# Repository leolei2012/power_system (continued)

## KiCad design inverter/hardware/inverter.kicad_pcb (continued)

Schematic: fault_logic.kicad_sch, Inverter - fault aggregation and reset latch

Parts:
C55: 10n; C_0402_1005Metric; Voltage_Rating 25V; MPN TBD
Q8: MMBT3904LT1G; onsemi_SOT-23_CASE318_Recommended; MPN MMBT3904LT1G
R73, R74: 10k; R_0402_1005Metric; Tolerance 1%; MPN TBD
R75: 100k; R_0402_1005Metric; Tolerance 1%; MPN TBD
TP14: FAULT_LATCH; TestPoint_Pad_D1.5mm
U22, U23, U24, U25: 74LVC08APW,118; TSSOP-14_4.4x5mm_P0.65mm; MPN 74LVC08APW,118
U27: 74LVC00APW,118; TSSOP-14_4.4x5mm_P0.65mm; MPN 74LVC00APW,118
U28: 74LVC74AD,118; SOIC-14_3.9x8.7mm_P1.27mm; MPN 74LVC74AD,118

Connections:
+3V3_INV: U28.1 (~R); also elsewhere on the board
/Hardware latch/ENABLE_N: U24.10, U27.3
/Hardware latch/FAULT_ACTIVE: R74.1, U27.6
/Hardware latch/FAULT_BASE: Q8.1 (B), R74.2, R75.1
/Hardware latch/FAULT_LATCH: TP14.1, U28.5 (Q)
/Hardware latch/HEALTH_ALL: U24.6, U24.9, U24.12, U27.4, U28.4 (~S)
/Hardware latch/HEALTH_CHAIN_1: U22.3, U22.4
/Hardware latch/HEALTH_CHAIN_2: U22.6, U22.9
/Hardware latch/HEALTH_CHAIN_3: U22.8, U22.12
/Hardware latch/HEALTH_CHAIN_4: U22.11, U23.1
/Hardware latch/HEALTH_CHAIN_5: U23.3, U23.4
/Hardware latch/HEALTH_CHAIN_6: U23.6, U23.9
/Hardware latch/HEALTH_CHAIN_7: U23.8, U23.12
/Hardware latch/HEALTH_CHAIN_8: U23.11, U24.1
/Hardware latch/HEALTH_CHAIN_9: U24.3, U24.4
/Hardware latch/HEALTH_UNLATCHED: U24.11, U25.1
/Hardware latch/NO_LATCH: U24.13, U27.5, U28.6 (~Q)
/Hardware latch/RESET_CLK: C55.1, R73.2, U28.3 (C)
/Hardware latch/RESET_REQUEST: R73.1, U24.8
AUX_FLT_N: U24.5; also elsewhere on the board
BASE_LOGIC_OK: U23.13; also elsewhere on the board
BUS_OV_OK: U23.5; also elsewhere on the board
DRIVE_PERMIT: U25.3; also elsewhere on the board
DRV_PG_LOGIC: U24.2; also elsewhere on the board
DRV_UV_OK: U23.10; also elsewhere on the board
ENABLE_QUALIFIED: U25.2, U27.1, U27.2; also elsewhere on the board
FAULT_N: Q8.3 (C); also elsewhere on the board
OC_U_HIGH_OK: U22.1; also elsewhere on the board
OC_U_LOW_OK: U22.2; also elsewhere on the board
OC_V_HIGH_OK: U22.5; also elsewhere on the board
OC_V_LOW_OK: U22.10; also elsewhere on the board
OC_W_HIGH_OK: U22.13; also elsewhere on the board
OC_W_LOW_OK: U23.2; also elsewhere on the board

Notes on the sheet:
HARDWARE HEALTH CHAIN / EVERY INPUT MUST REMAIN HIGH
FAULT MEMORY / DELIBERATE DISABLE-TO-RESET / PERMISSION
/S=HEALTH_ALL; /R held HIGH; D=0. Fault asynchronously sets Q. RESET_REQUEST = HEALTH_ALL AND NOT ENABLE_QUALIFIED. 10k / 10n delays the rising reset clock; hold ENABLE low >=1 ms after recovery. Fault or invalid supplies block DRIVE_PERMIT directly. Recovery with ENABLE high cannot clear the latch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

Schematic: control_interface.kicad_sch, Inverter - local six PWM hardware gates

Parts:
C56, C57, C58, C59, C60, C61: 100n; C_0402_1005Metric; Voltage_Rating 25V; MPN TBD
R76, R77, R78, R79, R80, R81, R82: 10k; R_0402_1005Metric; Tolerance 1%; MPN TBD
R83: 100k; R_0402_1005Metric; Tolerance 1%; MPN TBD
U22, U23, U24, U25, U26: 74LVC08APW,118; TSSOP-14_4.4x5mm_P0.65mm; MPN 74LVC08APW,118
U27: 74LVC00APW,118; TSSOP-14_4.4x5mm_P0.65mm; MPN 74LVC00APW,118

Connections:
+3V3_INV: C56.1, C57.1, C58.1, C59.1, C60.1, C61.1, U22.14 (VCC), U23.14 (VCC), U24.14 (VCC), U25.14 (VCC), U26.14 (VCC), U27.14 (VCC); also elsewhere on the board
DRIVE_PERMIT: R83.1, U25.5, U25.10, U25.13, U26.2, U26.5, U26.10; also elsewhere on the board
ENABLE_IN: R82.1; also elsewhere on the board
PWM_UH_IN: R76.1, U25.4; also elsewhere on the board
PWM_UL_IN: R77.1, U25.9; also elsewhere on the board
PWM_VH_IN: R78.1, U25.12; also elsewhere on the board
PWM_VL_IN: R79.1, U26.1; also elsewhere on the board
PWM_WH_IN: R80.1, U26.4; also elsewhere on the board
PWM_WL_IN: R81.1, U26.9; also elsewhere on the board
U_HIN: U25.6; also elsewhere on the board
U_LIN: U25.8; also elsewhere on the board
V_HIN: U25.11; also elsewhere on the board
V_LIN: U26.3; also elsewhere on the board
W_HIN: U26.6; also elsewhere on the board
W_LIN: U26.8; also elsewhere on the board

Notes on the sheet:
HARDWARE GATING / SIX PWM COMMANDS
LOGIC POWER / LOCAL DECOUPLING
DEFAULT DISABLE / NO PERMISSION
R76-R81: hold all six commands LOW while the controller is disconnected or Hi-Z. R82: default disabled. R83: default no permission. Logic levels remain 3.3 V; hardware AND gates operate independently of firmware.
C56-C61: 100 nF local bypass at each logic package.
U26D / U27C / U27D are used on the Base interlock page. R76-R81 default PWM LOW; R82 raw ENABLE default LOW. No MCU on this board; CTRL_READY must qualify ENABLE before any latch reset or DRIVE_PERMIT.

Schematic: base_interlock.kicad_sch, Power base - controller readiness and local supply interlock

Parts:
R160: 10k; R_0402_1005Metric; Tolerance 1%; MPN TBD
U26: 74LVC08APW,118; TSSOP-14_4.4x5mm_P0.65mm; MPN 74LVC08APW,118
U27: 74LVC00APW,118; TSSOP-14_4.4x5mm_P0.65mm; MPN 74LVC00APW,118

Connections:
/Base interlock/BASE_NOT_READY: U27.8, U27.12, U27.13
BASE_LOGIC_OK: U27.9; also elsewhere on the board
BASE_READY: U27.11; also elsewhere on the board
CTRL_READY: R160.1, U26.13; also elsewhere on the board
DRV_PG_LOGIC: U27.10; also elsewhere on the board
ENABLE_IN: U26.12; also elsewhere on the board
ENABLE_QUALIFIED: U26.11; also elsewhere on the board

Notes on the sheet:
REMOVABLE CONTROLLER / DEFAULT DISABLE
Common GND, 3.3 V logic. CTRL_READY comes from the controller reset-health buffer. The power base owns all PWM pull-downs and hardware permission; no MCU firmware is required to block a missing controller.
R160 = 10k. Unplugged, controller reset or lost controller power => ENABLE_QUALIFIED LOW. Only ENABLE_QUALIFIED enters the latch reset and DRIVE_PERMIT logic. Raw ENABLE_IN keeps its original local R82 pull-down.
BASE SUPPLY PRESENCE / INDEPENDENT OF OPEN-COLLECTOR FAULT
BASE_READY = BASE_LOGIC_OK AND DRV_PG_LOGIC. The MCU sub-board provides its receiver pull-down. FAULT_N remains Q8 open collector with a pull-up only in the MCU 3.3 V domain. A high FAULT_N alone does not prove base power. U26/U27 package power and 100 nF bypass stay on Hardware PWM gates. No added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

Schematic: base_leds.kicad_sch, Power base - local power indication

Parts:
D3: PWR; LED_0603_1608Metric; MPN TBD
R130: 2.2k; R_0402_1005Metric; Tolerance 1%; MPN TBD

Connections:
+3V3_INV: R130.1; also elsewhere on the board
/Base LEDs/LED_PWR_AN: D3.2 (A), R130.2

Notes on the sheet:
LOCAL POWER INDICATOR / NO MCU LED SIGNALS ACROSS HEADER
D3: base 3.3 V present. This lamp alone does not indicate driver power or protection permission. D4..D7 and R131..R134 belong to the removable MCU sub-board: RUN / FAULT / COMM / AUX. The power base has no MCU-run or communication LED nets on its board-to-board header.

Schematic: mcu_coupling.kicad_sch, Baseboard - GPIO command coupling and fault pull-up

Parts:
R135, R136, R137, R138, R139, R140, R141, R142: 33; R_0402_1005Metric; Tolerance 1%; MPN TBD
R143: 10k; R_0402_1005Metric; Tolerance 1%; MPN TBD

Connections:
+3V3_CORE_REF: R143.2; also elsewhere on the board
BRAKE_IN: R142.2; also elsewhere on the board
ENABLE_IN: R141.2; also elsewhere on the board
PA8: R135.1; also elsewhere on the board
PA9: R137.1; also elsewhere on the board
PA10: R139.1; also elsewhere on the board
PB12: R143.1; also elsewhere on the board
PB13: R136.1; also elsewhere on the board
PB14: R138.1; also elsewhere on the board
PB15: R140.1; also elsewhere on the board
PC4: R141.1; also elsewhere on the board
PC6: R142.1; also elsewhere on the board
PWM_UH_IN: R135.2; also elsewhere on the board
PWM_UL_IN: R136.2; also elsewhere on the board
PWM_VH_IN: R137.2; also elsewhere on the board
PWM_VL_IN: R138.2; also elsewhere on the board
PWM_WH_IN: R139.2; also elsewhere on the board
PWM_WL_IN: R140.2; also elsewhere on the board

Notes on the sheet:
CONTROLLER COMMAND SERIES RESISTORS / BASEBOARD SIGNALS
FAULT INPUT / LOCAL PULL-UP AND TIMER BKIN
Protected PB12 is TIM1 BKIN; pull-up uses the exported core 3V3 reference. NRST is debug-only; it is not a power-stage fault output. Six PWM, ENABLE and BRAKE series resistors remain local to the base.

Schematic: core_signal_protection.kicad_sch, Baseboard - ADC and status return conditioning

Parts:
C69, C70, C71, C72, C73, C74, C75, C76: 1n; C_0402_1005Metric; Voltage_Rating 16 V minimum; MPN TBD
D201, D202, D203, D204, D205, D206, D207, D208, D209, D210: BAT54S,215; Nexperia_SOT23_Reflow_Pad0.70x0.60mm; MPN BAT54S,215
R84, R85, R86, R87, R88, R89, R90, R91: 100; R_0402_1005Metric; Tolerance 1%; MPN TBD
R201, R202, R203, R204, R205, R206, R207, R208: 360; R_0603_1608Metric; Tolerance 1%; MPN TBD
R209: 10k; R_0603_1608Metric; MPN TBD
R210, R211: 1k; R_0603_1608Metric; Tolerance 1%; MPN TBD

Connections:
+3V3_CORE_REF: D201.2 (K2), D202.2 (K2), D203.2 (K2), D204.2 (K2), D205.2 (K2), D206.2 (K2), D207.2 (K2), D208.2 (K2), D209.2 (K2), D210.2 (K2); also elsewhere on the board
BASE_READY: R210.1; also elsewhere on the board
FAULT_N: R211.1; also elsewhere on the board
I_U_PORT: R201.1; also elsewhere on the board
I_V_PORT: R202.1; also elsewhere on the board
I_W_PORT: R203.1; also elsewhere on the board
unnamed: D201.3 (K1/A2), R84.1, R201.2
unnamed: D202.3 (K1/A2), R85.1, R202.2
unnamed: D203.3 (K1/A2), R86.1, R203.2
unnamed: D204.3 (K1/A2), R87.1, R204.2
unnamed: D205.3 (K1/A2), R88.1, R205.2
unnamed: D206.3 (K1/A2), R89.1, R206.2
unnamed: D207.3 (K1/A2), R90.1, R207.2
unnamed: D208.3 (K1/A2), R91.1, R208.2
PA4: C73.1, R88.2; also elsewhere on the board
PB0: C74.1, R89.2; also elsewhere on the board
PB1: C75.1, R90.2; also elsewhere on the board
PB2: C76.1, R91.2; also elsewhere on the board
PB12: D210.3 (K1/A2), R211.2; also elsewhere on the board
PC0: C69.1, R84.2; also elsewhere on the board
PC1: C70.1, R85.2; also elsewhere on the board
PC2: C71.1, R86.2; also elsewhere on the board
PC3: C72.1, R87.2; also elsewhere on the board
PC13: D209.3 (K1/A2), R209.1, R210.2; also elsewhere on the board
TEMP_NTC: R208.1; also elsewhere on the board
V_DC_PORT: R204.1; also elsewhere on the board
V_U_PORT: R205.1; also elsewhere on the board
V_V_PORT: R206.1; also elsewhere on the board
V_W_PORT: R207.1; also elsewhere on the board

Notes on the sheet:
STATUS RETURN LIMITING / CORE-REFERENCED CLAMPS
8 ADC PATHS / 360R CLAMP + 100R / 1n AT CORE SOCKET
I_U_PORT -> PC0
I_V_PORT -> PC1
I_W_PORT -> PC2
V_DC_PORT -> PC3
V_U_PORT -> PA4
V_V_PORT -> PB0
V_W_PORT -> PB1
TEMP_NTC -> PB2
Clamp upper rail returns ONLY through core 3V3_REF pins; never join it to base +3V3_INV. Power off both boards before mating.

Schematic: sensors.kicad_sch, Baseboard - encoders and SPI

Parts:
J9: ENC_A: PWR GND A B Z; HCTL_PZ127_1x05_P1.27mm_Drill0.70mm; MPN PZ127-1-05-Z
J10: ENC_B: PWR GND A B Z; HCTL_PZ127_1x05_P1.27mm_Drill0.70mm; MPN PZ127-1-05-Z
J11: SPI_A: PWR GND SCK MOSI MISO CS; HCTL_PZ127_1x06_P1.27mm_Drill0.70mm; MPN PZ127-1-06-Z
J12: SPI_B: PWR GND SCK MOSI MISO CS; HCTL_PZ127_1x06_P1.27mm_Drill0.70mm; MPN PZ127-1-06-Z
R94, R96, R98, R101, R103, R105: 100; R_0402_1005Metric; Tolerance 1%; MPN TBD
R95, R97, R99, R102, R104, R106, R112, R118: 10k; R_0402_1005Metric; Tolerance 1%; MPN TBD
R100, R107, R113, R119: 0; R_0402_1005Metric; Tolerance 1%; MPN TBD; not fitted
R108, R109, R110, R111, R114, R115, R116, R117: 33; R_0402_1005Metric; Tolerance 1%; MPN TBD

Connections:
+3V3_INV: R95.2, R97.2, R99.2, R102.2, R104.2, R106.2, R112.2, R118.2; also elsewhere on the board
+5V_SENSOR: R100.1, R107.1, R113.1, R119.1; also elsewhere on the board
/Encoders and SPI/ENC_A_A_PORT: J9.3, R94.1
/Encoders and SPI/ENC_A_B_PORT: J9.4, R96.1
/Encoders and SPI/ENC_A_VCC: J9.1, R100.2
/Encoders and SPI/ENC_A_Z_PORT: J9.5, R98.1
/Encoders and SPI/ENC_B_A_PORT: J10.3, R101.1
/Encoders and SPI/ENC_B_B_PORT: J10.4, R103.1
/Encoders and SPI/ENC_B_VCC: J10.1, R107.2
/Encoders and SPI/ENC_B_Z_PORT: J10.5, R105.1
/Encoders and SPI/SPI_A_CS_PORT: J11.6, R111.2
/Encoders and SPI/SPI_A_MISO_PORT: J11.5, R110.2
/Encoders and SPI/SPI_A_MOSI_PORT: J11.4, R109.2
/Encoders and SPI/SPI_A_SCK_PORT: J11.3, R108.2
/Encoders and SPI/SPI_A_VCC: J11.1, R113.2
/Encoders and SPI/SPI_B_CS_PORT: J12.6, R117.2
/Encoders and SPI/SPI_B_MISO_PORT: J12.5, R116.2
/Encoders and SPI/SPI_B_MOSI_PORT: J12.4, R115.2
/Encoders and SPI/SPI_B_SCK_PORT: J12.3, R114.2
/Encoders and SPI/SPI_B_VCC: J12.1, R119.2
PA0: R94.2, R95.1; also elsewhere on the board
PA1: R96.2, R97.1; also elsewhere on the board
PA2: R98.2, R99.1; also elsewhere on the board
PA3: R105.2, R106.1; also elsewhere on the board
PA5: R108.1; also elsewhere on the board
PA6: R110.1; also elsewhere on the board
PA7: R109.1; also elsewhere on the board
PA15: R111.1, R112.1; also elsewhere on the board
PB6: R101.2, R102.1; also elsewhere on the board
PB7: R103.2, R104.1; also elsewhere on the board
PC9: R117.1, R118.1; also elsewhere on the board
PC10: R114.1; also elsewhere on the board
PC11: R116.1; also elsewhere on the board
PC12: R115.1; also elsewhere on the board

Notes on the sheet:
ABZ ENCODER A / 3.3 V SINGLE-ENDED
DNP
100 ohm series / 10k pull-ups to 3.3 V. 5 V supply link DNP.
SPI SENSOR A / 3.3 V SINGLE-ENDED
ABZ ENCODER B / 3.3 V SINGLE-ENDED
SPI SENSOR B / 3.3 V SINGLE-ENDED
All external signal pins are 3.3 V single-ended; no 5 V level conversion or cable protection is claimed. R100 / R107 / R113 / R119 are DNP: external sensor-power links remain open by default.

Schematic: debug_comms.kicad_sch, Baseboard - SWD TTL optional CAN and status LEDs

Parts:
C82: 100n; C_0402_1005Metric; Voltage_Rating 16 V minimum; MPN TBD; not fitted
D4: LED_RUN; LED_0603_1608Metric; MPN TBD
D5: LED_FAULT; LED_0603_1608Metric; MPN TBD
D6: LED_COMM; LED_0603_1608Metric; MPN TBD
D7: LED_AUX; LED_0603_1608Metric; MPN TBD
J13: SWD: VTREF IO CLK GND NRST; HCTL_PZ127_1x05_P1.27mm_Drill0.70mm; MPN PZ127-1-05-Z
J14: TTL: TX RX GND; HCTL_PZ127_1x03_P1.27mm_Drill0.70mm; MPN PZ127-1-03-Z
J15: CAN: H L GND; HCTL_PZ127_1x03_P1.27mm_Drill0.70mm; MPN PZ127-1-03-Z; not fitted
R120, R121, R123: 33; R_0402_1005Metric; Tolerance 1%; MPN TBD
R124: 100; R_0402_1005Metric; Tolerance 1%; MPN TBD
R125: 10k; R_0402_1005Metric; Tolerance 1%; MPN TBD
R126, R127: 0; R_0402_1005Metric; Tolerance 1%; MPN TBD; not fitted
R128: 10k; R_0402_1005Metric; Tolerance 1%; MPN TBD; not fitted
R129: 120; R_0402_1005Metric; Tolerance 1%; MPN TBD; not fitted
R131, R132, R133, R134: 2.2k; R_0402_1005Metric; Tolerance 1%; MPN TBD
U31: SN65HVD232DR; SOIC-8_3.9x4.9mm_P1.27mm; MPN SN65HVD232DR; not fitted

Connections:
+3V3_CORE_REF: J13.1; also elsewhere on the board
+3V3_INV: C82.1, R125.2, R128.2, R131.1, R132.1, R133.1, R134.1, U31.3 (VCC); also elsewhere on the board
/SWD UART CAN and status/CAN_H: J15.1, R129.1, U31.7 (CANH)
/SWD UART CAN and status/CAN_L: J15.2, R129.2, U31.6 (CANL)
/SWD UART CAN and status/CAN_RX_PHY: R127.1, U31.4 (R)
/SWD UART CAN and status/CAN_TX_PHY: R126.2, R128.1, U31.1 (D)
/SWD UART CAN and status/LED_AN_1: D4.2 (A), R131.2
/SWD UART CAN and status/LED_AN_2: D5.2 (A), R132.2
/SWD UART CAN and status/LED_AN_3: D6.2 (A), R133.2
/SWD UART CAN and status/LED_AN_4: D7.2 (A), R134.2
/SWD UART CAN and status/SWCLK_PORT: J13.3, R121.1
/SWD UART CAN and status/SWDIO_PORT: J13.2, R120.1
/SWD UART CAN and status/UART_RX_PORT: J14.2, R124.1
/SWD UART CAN and status/UART_TX_PORT: J14.1, R123.2
NRST: J13.5; also elsewhere on the board
PA11: R127.2; also elsewhere on the board
PA12: R126.1; also elsewhere on the board
PA13: R120.2; also elsewhere on the board
PA14: R121.2; also elsewhere on the board
PB5: D7.1 (K); also elsewhere on the board
PB10: R123.1; also elsewhere on the board
PB11: R124.2, R125.1; also elsewhere on the board
PC5: D4.1 (K); also elsewhere on the board
PC8: D5.1 (K); also elsewhere on the board
PD2: D6.1 (K); also elsewhere on the board

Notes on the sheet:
SWD / OPEN-DRAIN RESET / BOOT
VTREF senses the core 3V3 reference. NRST goes only to the core reset domain. RESET / BOOT buttons are on the minimum-system core. Existing TTL PB10/PB11 is application UART, not the ROM USART3 pin pair.
TTL UART / USART3 / 3.3 V
TX/RX relative to this board; no RS-232 levels. No USB and no supply output on TTL connector.
OPTIONAL CLASSIC CAN / COMPLETE PHY BLOCK DNP
FOUR MCU STATUS INDICATORS / ACTIVE LOW

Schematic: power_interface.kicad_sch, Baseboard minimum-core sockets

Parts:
J101, J102: PM254V-12-32-H85; XFCN_PM254V-12-32-H85_2x16_P2.54mm_Vertical_Drill1.02mm; MPN PM254V-12-32-H85
TP16: FAULT_N; TestPoint_Pad_D1.5mm
TP17: ENABLE_IN; TestPoint_Pad_D1.5mm

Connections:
+3V3_CORE_REF: J101.22, J101.32; also elsewhere on the board
CTRL_READY: J102.10; also elsewhere on the board
ENABLE_IN: TP17.1; also elsewhere on the board
FAULT_N: TP16.1; also elsewhere on the board
NRST: J102.32; also elsewhere on the board
PA0: J101.5; also elsewhere on the board
PA1: J101.6; also elsewhere on the board
PA2: J101.7; also elsewhere on the board
PA3: J101.8; also elsewhere on the board
PA4: J101.9; also elsewhere on the board
PA5: J101.10; also elsewhere on the board
PA6: J101.11; also elsewhere on the board
PA7: J101.12; also elsewhere on the board
PA8: J101.13; also elsewhere on the board
PA9: J101.14; also elsewhere on the board
PA10: J101.15; also elsewhere on the board
PA11: J101.16; also elsewhere on the board
PA12: J101.17; also elsewhere on the board
PA13: J101.18; also elsewhere on the board
PA14: J101.19; also elsewhere on the board
PA15: J101.20; also elsewhere on the board
PB0: J101.23; also elsewhere on the board
PB1: J101.24; also elsewhere on the board
PB2: J101.25; also elsewhere on the board
PB5: J101.28; also elsewhere on the board
PB6: J101.29; also elsewhere on the board
PB7: J101.30; also elsewhere on the board
PB10: J102.3; also elsewhere on the board
PB11: J102.4; also elsewhere on the board
PB12: J102.5; also elsewhere on the board
PB13: J102.6; also elsewhere on the board
PB14: J102.7; also elsewhere on the board
PB15: J102.8; also elsewhere on the board
PC0: J102.11; also elsewhere on the board
PC1: J102.12; also elsewhere on the board
PC2: J102.13; also elsewhere on the board
PC3: J102.14; also elsewhere on the board
PC4: J102.15; also elsewhere on the board
PC5: J102.16; also elsewhere on the board
PC6: J102.17; also elsewhere on the board
PC8: J102.19; also elsewhere on the board
PC9: J102.20; also elsewhere on the board
PC10: J102.21; also elsewhere on the board
PC11: J102.22; also elsewhere on the board
PC12: J102.23; also elsewhere on the board
PC13: J102.24; also elsewhere on the board
PD2: J102.28; also elsewhere on the board

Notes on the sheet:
J101 / PA0-15 + PB0-7
J102 / PB8-15 + PC0-15 + PD/PF/NRST
64 contacts: 52 MCU signal pads + 2 core 5V feed + 2 core 3V3 reference + CTRL_READY + 7 GND.
All MCU GPIOs are exposed by port name. PG10 stays NRST; PF0/PF1 share optional HSE; PB8 shares BOOT.
PC7 is RUN_ARM when plugged into this power base. CTRL_READY = Schmitt-reset-ok AND PC7; default LOW.
Standalone core: regulated 4.75-5.25V at J101 pins1/3 and GND. Do not parallel independent 5V sources.
3V3 reference is core -> base clamps / fault pull-up / SWD sense only. Never parallel base and core regulators.
Application ABZ / SPI / UART / SWD / CAN / LEDs / ADC filters all reside on the power baseboard.
Nine unused socket contacts are NC on this base only; all corresponding GPIO pads remain exposed on the core.
60x60 POWER ABOVE / 60x60 CORE BELOW. Core TOP male -> power BOTTOM socket. Board gap / thermal / button access pending PCB.

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
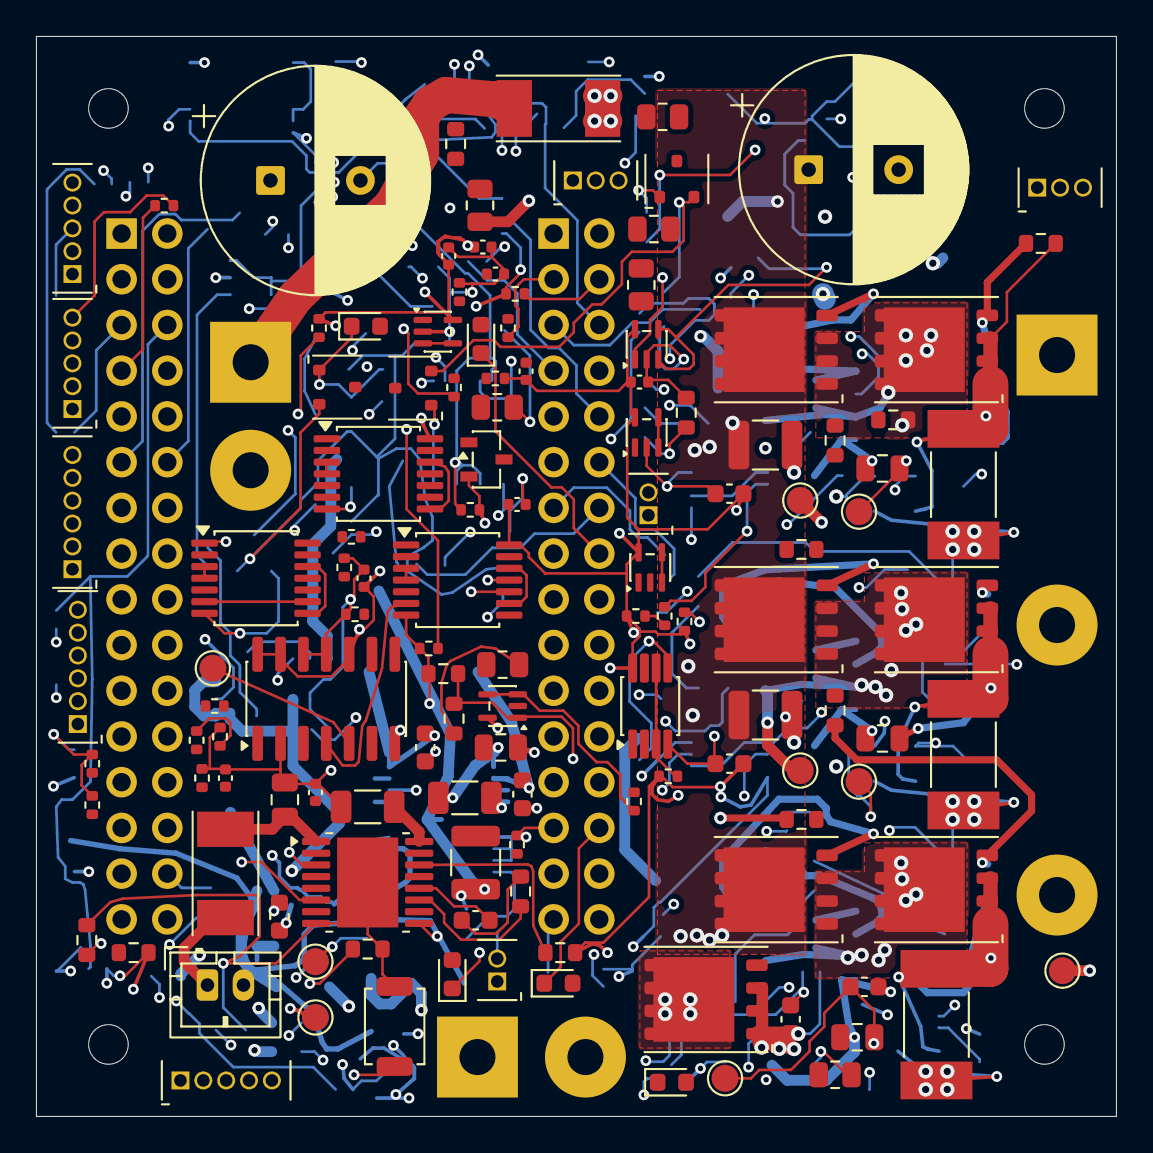
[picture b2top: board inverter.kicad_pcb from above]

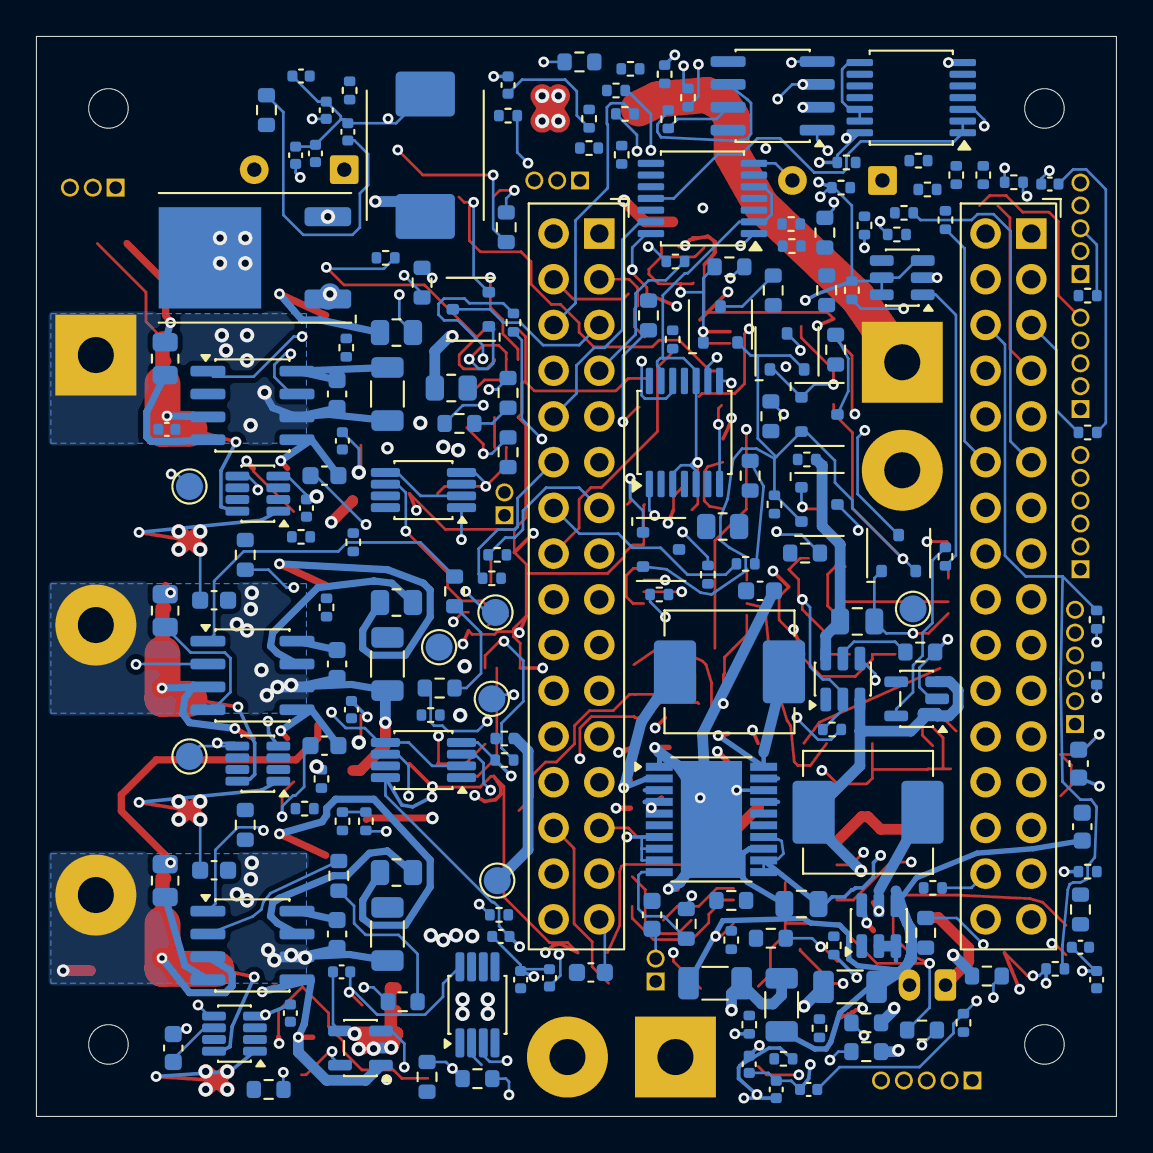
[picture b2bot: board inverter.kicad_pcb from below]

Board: 6 copper layers, 60.0 x 60.0 mm, 321 parts (187 on the bottom side), 220 nets.

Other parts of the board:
H1, H2, H3, H4: MountingHole_2.2mm_M2

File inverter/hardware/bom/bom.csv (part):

Reference,Value,Quantity,DNP,Sheet,Manufacturer,MPN,Supplier_PN,Purchase_URL,Footprint,Voltage_Rating,Tolerance,Design_Note,Selection_Status,Verification
C1,1u,1,no,/Auxiliary input/,YAGEO,TBD,,,Capacitor_SMD:C_0805_2012Metric,100V,,,value assigned; DC bias/MPN/LCSC pending,
C2,22n,1,no,/Auxiliary input/,YAGEO,TBD,,,Capacitor_SMD:C_0603_1608Metric,25V,,,value assigned; DC bias/MPN/LCSC pending,
C3,10u,1,no,/Auxiliary input/,YAGEO,TBD,,,Capacitor_SMD:C_1206_3216Metric,50V,,,value assigned; DC bias/MPN/LCSC pending,
F2,0451002.MRL,1,no,/Auxiliary input/,Littelfuse,0451002.MRL,C99547,https://item.szlcsc.com/100761.html,MyFootprints:Littelfuse_NANO2_451_476_Pad1.96x3.15mm_Gap2.95mm,,,,"Exact 2 A candidate fits current Nano2 451/453 footprint; converter inrush, short-circuit coordination and ambient derating remain application checks.",reviewed
J2,XT30PW-M30.G.Y,1,no,/Auxiliary input/,AMASS,XT30PW-M30.G.Y,C431092,https://item.szlcsc.com/426930.html,MyFootprints:JST_PH_B2B-PH-K_1x02_P2.00mm_Vertical,,,辅助电源输入（原 J2 AUX: +12..24V / GND）；Issue 简称 XT30PW-M；M30 为焊脚约 3.0 mm 高度，不是 30 A；现图封装尚未更新，待 #3。 人民币单价（SMT-CNY，嘉立创 SMT 的 LCSC 详情页 https://www.jlc-smt.com/lcsc/detail/C431092.html）：1 只 2.35 元，10 只 2.05 元；LCSC 国际站库存：70547 只（来源：https://wmsc.lcsc.com/ftps/wm/product/detail?productCode=C43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 00:40–00:46（Asia/Shanghai，CST）。,定案已定，待 #3 原理图更新位号/封装,reviewed
R1,78.7k,1,no,/Auxiliary input/,YAGEO,TBD,,,Resistor_SMD:R_0603_1608Metric,,0.1%,,value assigned; exact MPN/LCSC pending,
R2,10k,1,no,/Auxiliary input/,YAGEO,TBD,,,Resistor_SMD:R_0603_1608Metric,,0.1%,,value assigned; exact MPN/LCSC pending,
R3,221k,1,no,/Auxiliary input/,YAGEO,TBD,,,Resistor_SMD:R_0603_1608Metric,,0.1%,,value assigned; exact MPN/LCSC pending,
R4,10k,1,no,/Auxiliary input/,YAGEO,TBD,,,Resistor_SMD:R_0603_1608Metric,,0.1%,,value assigned; exact MPN/LCSC pending,
R5,402k,1,no,/Auxiliary input/,YAGEO,TBD,,,Resistor_SMD:R_0603_1608Metric,,1%,402k selects current-limit latch-off; direct RTN would select auto-retry,value assigned; exact MPN/LCSC pending,
R6,7.87k,1,no,/Auxiliary input/,YAGEO,TBD,,,Resistor_SMD:R_0603_1608Metric,,1%,Nominal 11.8k/R -> 1.50 A; tolerance/SOA/startup review,value assigned; exact MPN/LCSC pending,
R7,10k,1,no,/Auxiliary input/,YAGEO,TBD,,,Resistor_SMD:R_0603_1608Metric,,1%,,value assigned; exact MPN/LCSC pending,
R8,100k,1,yes,/Auxiliary input/,YAGEO,TBD,,,Resistor_SMD:R_0603_1608Metric,,1%,"DNP: remove external 12..24V SHDN pullup. TPS26600 internal SHDN bias is nominal 2.7V, recommended SHDN 0..4V. SW1 still pulls to EFUSE_RTN.","compact revision electrical correction; retain footprint, do not populate",
SW1,AUX_RESET,1,no,/Auxiliary input/,XUNPU,TS-1088-AR02016,C720477,https://item.szlcsc.com/763484.html,MyFootprints:SW_SPST_TS-1088-xR020,,,,Exact small SMD normally-open momentary 2-terminal switch; standard local footprint matches current manufacturer drawing. SW1 bias condition below remains an electrical-review hold point.,reviewed
U1,TPS26600PWPR,1,no,/Auxiliary input/,TI,TPS26600PWPR,C544399,https://item.szlcsc.com/565050.html,MyFootprints:HTSSOP-16-1EP_4.4x5mm_P0.65mm_EP3.4x5mm_Mask2.66x2.46mm,,,,,reviewed
C4,100n,1,no,/Driver supply/,YAGEO,CC0603KRX7R9BB104,C14663,https://item.szlcsc.com/15331.html,MyFootprints:C_0603_1608Metric,50V,10%,,C14663; 50V X7R covers original 25V local decoupling/bootstrap requirement; application transient and DC-bias verification pending,reviewed
C5,100n,1,no,/Driver supply/,YAGEO,CC0603KRX7R9BB104,C14663,https://item.szlcsc.com/15331.html,MyFootprints:C_0603_1608Metric,50V,10%,,C14663; 50V X7R covers original 25V local decoupling/bootstrap requirement; application transient and DC-bias verification pending,reviewed
C6,10u,1,no,/Driver supply/,YAGEO,TBD,,,Capacitor_SMD:C_1206_3216Metric,50V,,,value assigned; DC bias/MPN/LCSC pending,
C7,470n,1,no,/Driver supply/,YAGEO,TBD,,,Capacitor_SMD:C_0805_2012Metric,50V,,,value assigned; DC bias/MPN/LCSC pending,
C8,22u,1,no,/Driver supply/,YAGEO,TBD,,,Capacitor_SMD:C_1210_3225Metric,25V,,,value assigned; DC bias/MPN/LCSC pending,
C9,100n,1,no,/Driver supply/,YAGEO,CC0603KRX7R9BB104,C14663,https://item.szlcsc.com/15331.html,MyFootprints:C_0603_1608Metric,50V,10%,,C14663; 50V X7R covers original 25V local decoupling/bootstrap requirement; application transient and DC-bias verification pending,reviewed
C10,4.7u,1,no,/Driver supply/,YAGEO,TBD,,,Capacitor_SMD:C_0805_2012Metric,10V,,,value assigned; DC bias/MPN/LCSC pending,
L1,4.7uH,1,no,/Driver supply/,Sunlord,MWSA0603S-4R7MT,C408447,https://so.szlcsc.com/global.html?k=MWSA0603S-4R7MT,MyFootprints:L_Sunlord_MWSA0603S,,,,"Meets requested nominal L, current-table and DCR targets; auxiliary-converter operating/thermal qualification pending.",reviewed
R9,100k,1,no,/Driver supply/,YAGEO,TBD,,,Resistor_SMD:R_0603_1608Metric,,1%,,value assigned; exact MPN/LCSC pending,
R10,10k,1,no,/Driver supply/,YAGEO,TBD,,,Resistor_SMD:R_0603_1608Metric,,1%,,value assigned; exact MPN/LCSC pending,
R11,10k,1,no,/Driver supply/,YAGEO,TBD,,,Resistor_SMD:R_0603_1608Metric,,1%,,value assigned; exact MPN/LCSC pending,
R12,20k,1,no,/Driver supply/,YAGEO,TBD,,,Resistor_SMD:R_0603_1608Metric,,1%,,value assigned; exact MPN/LCSC pending,
TP1,+12V_DRV,1,no,/Driver supply/,,,,,TestPoint:TestPoint_Pad_D1.5mm,,,,,
TP2,BB_VREG,1,no,/Driver supply/,,,,,TestPoint:TestPoint_Pad_D1.5mm,,,,,
TP3,DRV_PG_LOGIC,1,no,/Driver supply/,,,,,TestPoint:TestPoint_Pad_D1.5mm,,,,,
U2,TPS55165QPWPRQ1,1,no,/Driver supply/,TI,TPS55165QPWPRQ1,C2071629,https://item.szlcsc.com/2163212.html,MyFootprints:TI_PWP0020W_HTSSOP-20_4.4x6.5mm_P0.65mm_EP2.79x3.64mm,,,,,reviewed
C11,10u,1,no,/Logic and sensors/,YAGEO,TBD,,,Capacitor_SMD:C_1206_3216Metric,50V,,,value assigned; DC bias/MPN/LCSC pending,
C12,100n,1,no,/Logic and sensors/,YAGEO,CC0603KRX7R9BB104,C14663,https://item.szlcsc.com/15331.html,MyFootprints:C_0603_1608Metric,50V,10%,,C14663; 50V X7R covers original 25V local decoupling/bootstrap requirement; application transient and DC-bias verification pending,reviewed
C13,22u,1,no,/Logic and sensors/,YAGEO,TBD,,,Capacitor_SMD:C_1206_3216Metric,16V,,,value assigned; DC bias/MPN/LCSC pending,
C14,22u,1,no,/Logic and sensors/,YAGEO,TBD,,,Capacitor_SMD:C_1206_3216Metric,16V,,,value assigned; DC bias/MPN/LCSC pending,
C15,1u,1,no,/Logic and sensors/,YAGEO,TBD,,,Capacitor_SMD:C_0603_1608Metric,25V,,,value assigned; DC bias/MPN/LCSC pending,
C16,2.2u,1,no,/Logic and sensors/,YAGEO,TBD,,,Capacitor_SMD:C_0603_1608Metric,25V,,,value assigned; DC bias/MPN/LCSC pending,
C17,100n,1,no,/Logic and sensors/,YAGEO,TBD,,,Capacitor_SMD:C_0402_1005Metric,25V,,,value assigned; DC bias/MPN/LCSC pending,
C18,10u,1,no,/Logic and sensors/,YAGEO,TBD,,,Capacitor_SMD:C_0805_2012Metric,16V,,,value assigned; DC bias/MPN/LCSC pending,
J7,OPTIONAL SENSOR 5V / GND,1,yes,/Logic and sensors/,HCTL,PZ127-1-02-Z,C5372825,https://item.szlcsc.com/6225189.html,MyFootprints:HCTL_PZ127_1x02_P1.27mm_Drill0.70mm,,,,compact mechanical engineering candidate; original pin order retained,reviewed
L2,4.7uH,1,no,/Logic and sensors/,Sunlord,MWSA0603S-4R7MT,C408447,https://so.szlcsc.com/global.html?k=MWSA0603S-4R7MT,MyFootprints:L_Sunlord_MWSA0603S,,,,"Meets requested nominal L, current-table and DCR targets; auxiliary-converter operating/thermal qualification pending.",reviewed
R13,10k,1,no,/Logic and sensors/,YAGEO,TBD,,,Resistor_SMD:R_0402_1005Metric,,1%,,value assigned; exact MPN/LCSC pending,
R14,49.9k,1,no,/Logic and sensors/,YAGEO,TBD,,,Resistor_SMD:R_0603_1608Metric,,1%,~0.475..0.582 A datasheet min/max formula at nominal R; resistor tolerance adds error,value assigned; exact MPN/LCSC pending,
R15,10k,1,no,/Logic and sensors/,YAGEO,TBD,,,Resistor_SMD:R_0603_1608Metric,,1%,,value assigned; exact MPN/LCSC pending,
TP4,SENSOR_PWR_FLT_N,1,no,/Logic and sensors/,,,,,TestPoint:TestPoint_Pad_D1.5mm,,,,,
U3,AP63205WU-7,1,no,/Logic and sensors/,Diodes,AP63205WU-7,C2071056,https://item.szlcsc.com/2162639.html,MyFootprints:TSOT-23-6,,,,,reviewed
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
